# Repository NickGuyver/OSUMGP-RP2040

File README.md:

# OSUMGP-RP2040

**OSUMGP-RP2040**: **Open Source Universal Modern Game Pad - RP2040 Edition**. This project is a reference design for building a game pad utilizing the GP2040-CE firmware, specifically tailored for the RP2040 microcontroller.

KiCanvas link so you don't have to download to just review the files is [here](https://kicanvas.org/?github=https%3A%2F%2Fgithub.com%2FNickGuyver%2FOSUMGP-RP2040)

## Current Status
- **Beta**: The project is currently in beta. Feedback and contributions to improve the design and functionality are appreciated.
- **Case**: [RAF](https://github.com/RAF-no-desu) generously created a 3D printable case [here](https://www.printables.com/model/1000656-universal-modern-game-pad-w-usb-passthrough-osumgp)
- **Firmware**: Latest release of GP2040-CE firmware is [here](https://github.com/OpenStickCommunity/GP2040-CE/releases/latest/download/GP2040-CE_0.7.10_OSUMGP-RP2040.uf2)

## Features
- **Open Source**: Fully open-source design and firmware for community collaboration and customization.
- **RP2040 Microcontroller**: Leverages the powerful and versatile RP2040, the same chip used in the Raspberry Pi Pico.
- **GP2040-CE Firmware**: Compatible with the GP2040-CE firmware, providing robust support for many consoles and devices.
- **Customizable**: Easily adaptable for various game pad layouts and configurations.

## Pinout Summary
- See [GP2040-CE Usage](https://gp2040-ce.info/usage/) for reference between modes

| RP2040 Pin | Action     | PCB        |
|------------|------------|------------|
| 17         | Up         | S4         |
| 13         | Down       | S1         |
| 14         | Right      | S2         |
| 16         | Left       | S3         |
| 9          | B1         | S5         |
| 8          | B2         | S6         |
| 7          | R2         | S18        |
| 18         | L2         | S17        |
| 6          | B3         | S7         |
| 5          | B4         | S8         |
| 3          | R1         | S16        |
| 21         | L1         | S15        |
| 22         | S1         | S9         |
| 2          | S2         | S10        |
| 19         | L3         | SW3        |
| 10         | R3         | SW4        |
| 15         | A1         | S14        |
| 20         | A2         | S11        |
| 26         | LS - X     | SW3        |
| 28         | LS - Y     | SW3        |
| 27         | RS - X     | SW4        |
| 29         | RS - Y     | SW4        |

| RP2040 Pin | Function   | PCB        |
|------------|------------|------------|
| 0          | SDA        | J2         |
| 1          | SCL        | J2         |
| 11         | USB D+     | J3         |
| 12         | USB D-     | J3         |

## Thanks
Special thanks to the [Alpakka](https://inputlabs.io/alpakka) and [GP2040-CE](https://gp2040-ce.info/) projects, as well as the many people in the community who provided help and guidance.

## License
This project is licensed under the Creative Commons Attribution 4.0 International License - see the [LICENSE](LICENSE) file for details.

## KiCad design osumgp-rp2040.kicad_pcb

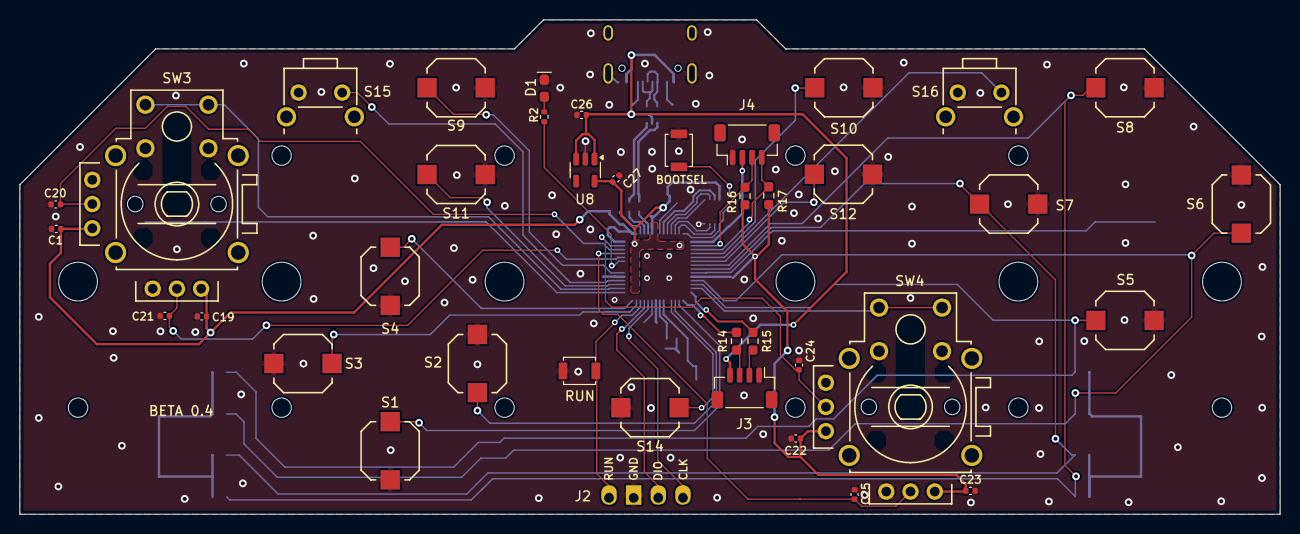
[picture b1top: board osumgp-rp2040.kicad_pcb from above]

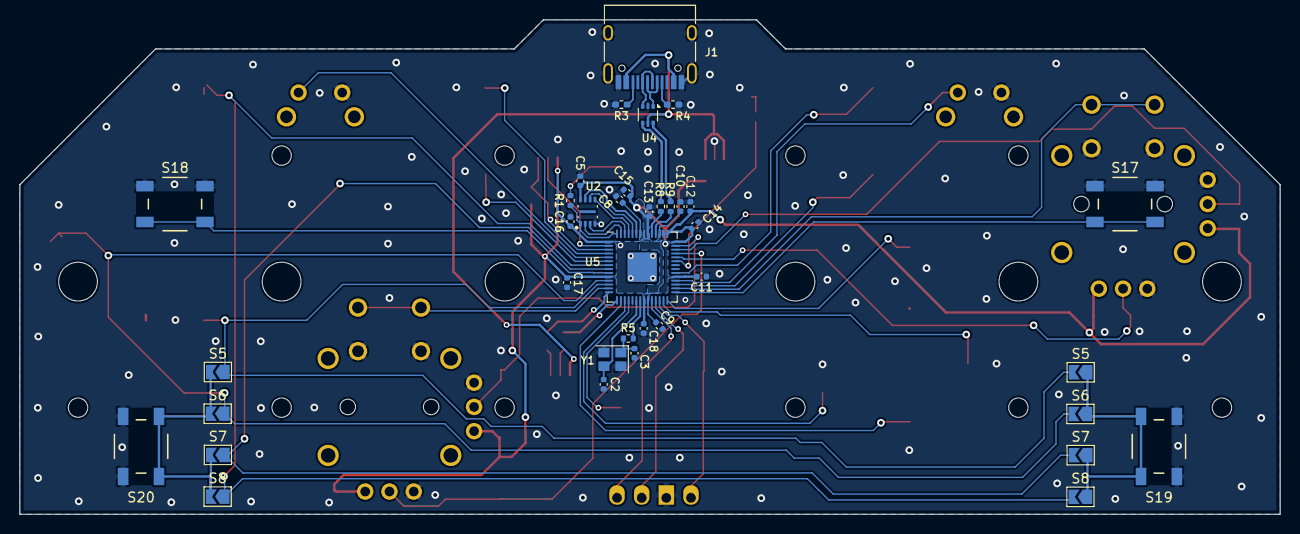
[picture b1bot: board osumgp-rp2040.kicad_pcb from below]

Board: 2 copper layers, 130.0 x 51.0 mm, 76 parts (37 on the bottom side), 58 nets.

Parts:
C1, C5, C8, C9, C11, C13, C14, C15, C16, C17, C18, C19, C20, C21, C22, C23, C24, C25: 100nF; C_0402_1005Metric
C2, C3: 18pF; C_0402_1005Metric
C10, C12, C26, C27: 1uF; C_0402_1005Metric
D1: LED; LED_0603_1608Metric_Pad1.05x0.95mm_HandSolder
J1: USB_C_Receptacle_USB2.0; USB_C_Receptacle_HRO_TYPE-C-31-M-12
J2: SWD; Pico_4pin
J3: USB; JST_SH_BM04B-SRSS-TB_1x04-1MP_P1.00mm_Vertical
J4: I2C; JST_SH_BM04B-SRSS-TB_1x04-1MP_P1.00mm_Vertical
JP2, JP6: S5; SolderJumper-2_P1.3mm_Open_TrianglePad1.0x1.5mm
JP3, JP7: S6; SolderJumper-2_P1.3mm_Open_TrianglePad1.0x1.5mm
JP4, JP8: S7; SolderJumper-2_P1.3mm_Open_TrianglePad1.0x1.5mm
JP5, JP9: S8; SolderJumper-2_P1.3mm_Open_TrianglePad1.0x1.5mm
R1, R2, R5: 1kΩ; R_0402_1005Metric
R3, R4: 5.1kΩ; R_0402_1005Metric_Pad0.72x0.64mm_HandSolder
R8, R9: 27Ω; R_0402_1005Metric
R14, R15: 22Ω; R_0603_1608Metric_Pad0.98x0.95mm_HandSolder
R16, R17: 2.2kΩ; R_0603_1608Metric_Pad0.98x0.95mm_HandSolder
S1, S2, S3, S4, S5, S6, S7, S8, S9, S10, S11, S12, S14: Face Button; Alpsalpine_SKPM
S15, S16: Shoulder Button; Alpsalpine_SKHHL
S17, S18, S19, S20: Back Button; Alpsalpine_SKQG
SW1: BOOTSEL; SW_SPST_B3U-1000P
SW2: RST; SW_SPST_B3U-1000P
SW3, SW4: Alpsalpine_RKJXV; Alpsalpine_RKJXV122400R
U2: W25Q16JVUXIQ; IC_W25Q16JVUXIQ_TR
U4: USBLC6-2P6; SOT-666
U5: RP2040; RP2040-QFN-56
U8: AP2112K-3.3; SOT-23-5
Y1: ECS-120-12-36-AGN-TR3; Crystal_SMD_2520-4Pin_2.5x2.0mm

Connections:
+1V1: C8.1, C9.1, C10.1, U5.23 (DVDD), U5.45 (VREG_VOUT), U5.50 (DVDD)
+3V3: C1.2, C5.1, C11.1, C12.1, C13.1, C14.1, C15.1, C16.1, C17.1, C18.1, C19.1, C22.2, C23.1, C27.1, J4.2 (3V3), R16.1, R17.1, SW3.3 (VCC0), SW3.6 (VCC1), SW4.3 (VCC0), SW4.6 (VCC1), U2.8 (VCC), U5.1 (IOVDD), U5.10 (IOVDD), U5.22 (IOVDD), U5.33 (IOVDD), U5.42 (IOVDD), U5.43 (ADC_AVDD), U5.44 (VREG_IN), U5.48 (USB_VDD), U5.49 (IOVDD), U8.5 (VOUT)
+5V: C26.1, J1.A4 (VBUS), J1.A9 (VBUS), J1.B4 (VBUS), J1.B9 (VBUS), J3.4 (VCC), U4.5 (VBUS), U8.1 (VIN), U8.3 (EN)
/BUTTON_A1: S14.2, U5.18 (GPIO15)
/BUTTON_A2: S11.2, U5.31 (GPIO20)
/BUTTON_B1: JP2.2 (B), JP6.1 (A), S5.2, U5.12 (GPIO9)
/BUTTON_B2: JP3.2 (B), JP7.1 (A), S6.2, U5.11 (GPIO8)
/BUTTON_B3: JP4.2 (B), JP8.1 (A), S7.2, U5.8 (GPIO6)
/BUTTON_B4: JP5.2 (B), JP9.1 (A), S8.2, U5.7 (GPIO5)
/BUTTON_DOWN: S1.2, U5.16 (GPIO13)
/BUTTON_L1: S15.2, U5.32 (GPIO21)
/BUTTON_L2: S17.2, U5.29 (GPIO18)
/BUTTON_L3: SW3.8 (B), SW3.10 (D), U5.30 (GPIO19)
/BUTTON_LEFT: S3.2, U5.27 (GPIO16)
/BUTTON_R1: S16.2, U5.5 (GPIO3)
/BUTTON_R2: S18.2, U5.9 (GPIO7)
/BUTTON_R3: SW4.8 (B), SW4.10 (D), U5.13 (GPIO10)
/BUTTON_RIGHT: S2.2, U5.17 (GPIO14)
/BUTTON_S1: S9.2, U5.34 (GPIO22)
/BUTTON_S2: S10.2, U5.4 (GPIO2)
/BUTTON_UP: S4.2, U5.28 (GPIO17)
/D+: R8.1, U4.4 (I/O2)
/D-: R9.1, U4.6 (I/O1)
/DN: R9.2, U5.46 (USB_DM)
/DP: R8.2, U5.47 (USB_DP)
/GPIO4: S12.2, U5.6 (GPIO4)
/GPIO25: R2.1, U5.37 (GPIO25)
/I2C0_SCL: J4.4 (SCL), R17.2, U5.3 (GPIO1)
/I2C0_SDA: J4.3 (SDA), R16.2, U5.2 (GPIO0)
/QSPI_SCLK: U2.6 (CLK), U5.52 (QSPI_SCLK)
/QSPI_SD0: U2.5 (DI(IO0)), U5.53 (QSPI_SD0)
/QSPI_SD1: U2.2 (DO(IO1)), U5.55 (QSPI_SD1)
/QSPI_SD2: U2.3 (IO2), U5.54 (QSPI_SD2)
/QSPI_SD3: U2.7 (IO3), U5.51 (QSPI_SD3)
/QSPI_SS: R1.1, U2.1 (~CS), U5.56 (QSPI_SS)
/RUN: J2.4, SW2.1, U5.26 (RUN)
/SWCLK: J2.1, U5.24 (SWCLK)
/SWD: J2.2, U5.25 (SWD)
/THUMBSTICK_LEFT_X: C21.2, SW3.5 (ADC1), U5.38 (GPIO26_ADC0)
/THUMBSTICK_LEFT_Y: C20.2, SW3.2 (ADC0), U5.40 (GPIO28_ADC2)
/THUMBSTICK_RIGHT_X: C25.2, SW4.5 (ADC1), U5.39 (GPIO27_ADC1)
/THUMBSTICK_RIGHT_Y: C24.2, SW4.2 (ADC0), U5.41 (GPIO29_ADC3)
/USBD+: J1.A6 (D+), J1.B6 (D+), U4.3 (I/O2)
/USBD-: J1.A7 (D-), J1.B7 (D-), U4.1 (I/O1)
/USBH_DN: R14.2, U5.15 (GPIO12)
/USBH_DP: R15.1, U5.14 (GPIO11)
/XIN: C2.1, U5.20 (XIN), Y1.3
/XOUT: R5.1, U5.21 (XOUT)
GND: C1.1, C2.2, C3.2, C5.2, C8.2, C9.2, C10.2, C11.2, C12.2, C13.2, C14.2, C15.2, C16.2, C17.2, C18.2, C19.2, C20.1, C21.1, C22.1, C23.2, C24.1, C25.1, C26.2, C27.2, D1.1 (K), J1.A1 (GND), J1.A12 (GND), J1.B1 (GND), J1.B12 (GND), J1.S1 (SHIELD), J2.3, J3.1 (GND), J4.1 (GND), R3.2, R4.2, S1.1, S2.1, S3.1, S4.1, S5.1, S6.1, S7.1, S8.1, S9.1, S10.1, S11.1, S12.1, S14.1, S15.1, S16.1, S17.1, S18.1, S19.1, S20.1, SW1.1, SW2.2, SW3.1 (GND0), SW3.4 (GND1), SW3.7 (A), SW3.9 (C), SW4.1 (GND0), SW4.4 (GND1), SW4.7 (A), SW4.9 (C), U2.4 (GND), U4.2 (GND), U5.19 (TESTEN), U5.57 (GND), U8.2 (GND), Y1.2, Y1.4
unnamed: C3.1, R5.2, Y1.1
unnamed: D1.2 (A), R2.2
unnamed: J1.A5 (CC1), R4.1
unnamed: J1.B5 (CC2), R3.1
unnamed: J3.2 (D+), R15.2
unnamed: J3.3 (D-), R14.1
unnamed: JP2.1 (A), JP3.1 (A), JP4.1 (A), JP5.1 (A), S19.2
unnamed: JP6.2 (B), JP7.2 (B), JP8.2 (B), JP9.2 (B), S20.2
unnamed: R1.2, SW1.2

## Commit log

2024-06-24 Add .gitignore
2024-06-24 Adust trace widths, component placement, and routing to pass DRC
2024-06-24 fix edge cut
2024-06-24 Fix DRC
2024-07-20 beta 0.4
    - copper to edge clearance 0.38mm
    - fix thin +3.3V traces
    - add more GND around the RP2040
    - connected mounting pads to GND
    - add more GND stitching
    - reduce plane fingers
2024-07-28 Update LICENSE
2024-08-31 fix led
2024-10-17 Update README.md
    Add KiCanvas link
